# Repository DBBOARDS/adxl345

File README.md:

# adxl345
These are the eagle files for DB Boards' SPI adxl345 breakout

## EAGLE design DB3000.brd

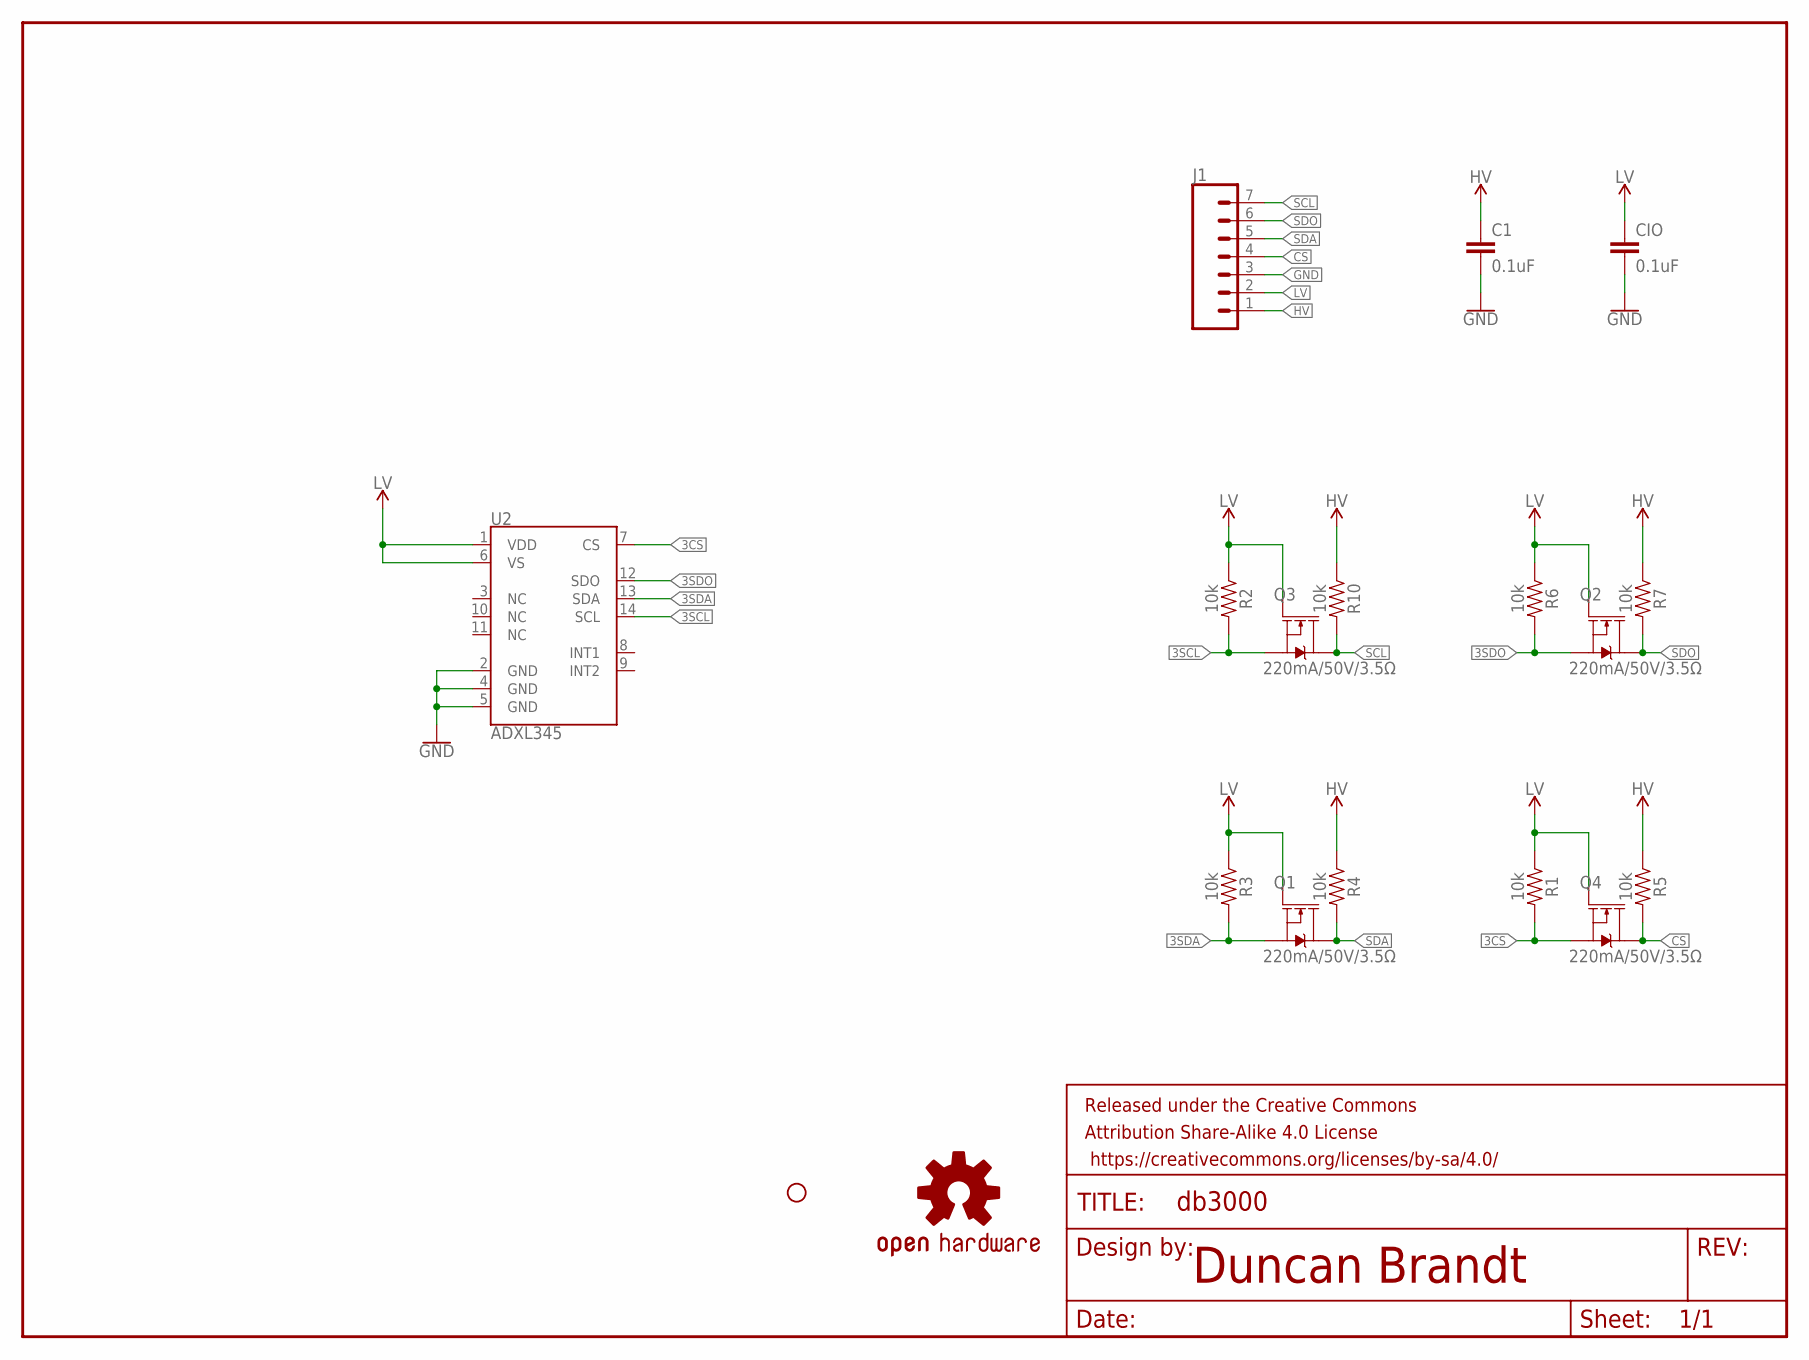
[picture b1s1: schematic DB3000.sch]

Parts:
C1: 0.1uF; 0603
CIO: 0.1uF; 0603
FRAME1: FRAME-LETTER; CREATIVE_COMMONS
J1: CONN_07; 1X07
JP3: STAND-OFF
LOGO1: OSHW-LOGOL; OSHW-LOGO-L
Q1, Q2, Q3, Q4: 220mA/50V/3.5Ω; SOT23-3
R1, R2, R3, R4, R5, R6, R7, R10: 10k; 0603
U2: ADXL345; LGA-14

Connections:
3CS: Q4.2 (S), R1.2, U2.7 (CS)
3SCL: Q3.2 (S), R2.2, U2.14 (SCL)
3SDA: Q1.2 (S), R3.2, U2.13 (SDA)
3SDO: Q2.2 (S), R6.2, U2.12 (SDO)
CS: J1.4, Q4.3 (D), R5.2
GND: C1.2, CIO.2, J1.3, U2.2 (GND), U2.4 (GND), U2.5 (GND)
HV: C1.1, J1.1, R4.1, R5.1, R7.1, R10.1
LV: CIO.1, J1.2, Q1.1 (G), Q2.1 (G), Q3.1 (G), Q4.1 (G), R1.1, R2.1, R3.1, R6.1, U2.1 (VDD), U2.6 (VS)
SCL: J1.7, Q3.3 (D), R10.2
SDA: J1.5, Q1.3 (D), R4.2
SDO: J1.6, Q2.3 (D), R7.2

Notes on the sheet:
Duncan Brandt

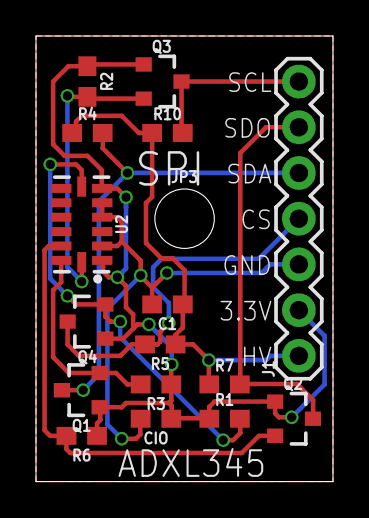
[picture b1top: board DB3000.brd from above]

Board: 2 copper layers, 16.5 x 24.8 mm, 19 parts (1 on the bottom side), 11 nets.

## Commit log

2018-01-10 DB Boards SPI adxl345 eagle files

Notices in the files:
parts and their libraries:
DB-HARDWARE: Licensing: Creative Commons ShareAlike 4.0 International - https://creativecommons.org/licenses/by-sa/4.0
DB-SYMBOLS: Released under the Creative Commons Attribution Share-Alike 4.0 License
DB-SYMBOLS: https://creativecommons.org/licenses/by-sa/4.0
